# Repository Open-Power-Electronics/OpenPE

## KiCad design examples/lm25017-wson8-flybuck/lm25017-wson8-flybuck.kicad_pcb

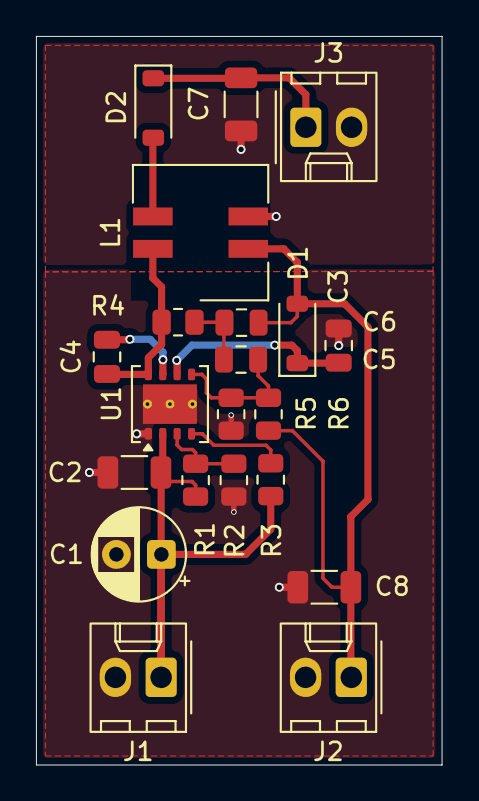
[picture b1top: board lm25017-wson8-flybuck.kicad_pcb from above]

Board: 2 copper layers, 22.5 x 40.5 mm, 21 parts (0 on the bottom side), 13 nets.

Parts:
C1: 2.2uF; CP_Radial_D5.0mm_P2.50mm
C2: 0.47uF; C_1206_3216Metric
C3: 0.1uF; C_0805_2012Metric
C4: 0.01uF; C_0805_2012Metric
C5: 10nF; C_0805_2012Metric
C6: 1nF; C_0805_2012Metric
C7: 2.2uF; C_1206_3216Metric
C8: 4.7uF; C_1206_3216Metric
D1, D2: D; D_SOD-123
J1, J2, J3: Conn_01x02; Molex_KK-254_AE-6410-02A_1x02_P2.54mm_Vertical
L1: 100uH; L_Wurth_WE-DD-7345straight
R1: 127k; R_0805_2012Metric
R2: 11.8k; R_0805_2012Metric
R3: 124k; R_0805_2012Metric
R4: 46.4k; R_0805_2012Metric
R5: 100k; R_0805_2012Metric
R6: 24.9k; R_0805_2012Metric
U1: LM25017; WSON-8-1EP_4x4mm_P0.8mm_EP2.2x3mm_ThermalVias

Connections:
/VIN: C1.1, C2.1, J1.1, R1.2, R3.1, U1.2
/VOUT1: C6.1, C8.1, D1.2, J2.1, L1.2, R5.1
/VOUT2: C7.1, D2.1, J3.1
GND: C1.2, C2.2, C3.2, C8.2, J1.2, J2.2, R2.1, R6.2, U1.1, U1.9
GND2: C7.2, J3.2, L1.3
unnamed: C5.1, C6.2, R4.2
unnamed: C3.1, D1.1, U1.6
unnamed: D2.2, L1.4
unnamed: C4.2, U1.7
unnamed: C5.2, R5.2, R6.1, U1.5
unnamed: R3.2, U1.4
unnamed: C4.1, L1.1, R4.1, U1.8
unnamed: R1.1, R2.2, U1.3

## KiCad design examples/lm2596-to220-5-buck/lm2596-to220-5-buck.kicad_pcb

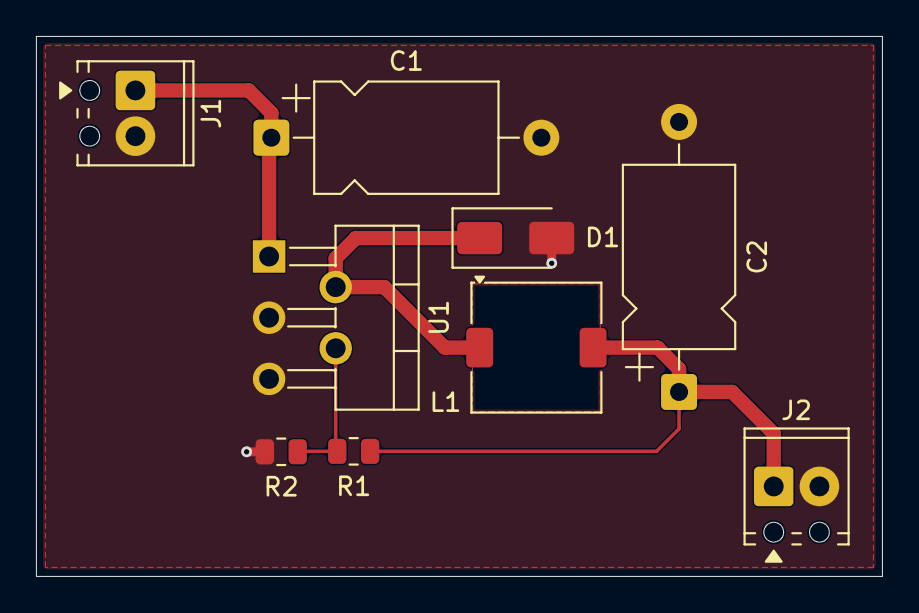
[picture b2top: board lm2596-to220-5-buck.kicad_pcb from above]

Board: 2 copper layers, 47.0 x 30.0 mm, 9 parts (0 on the bottom side), 5 nets.

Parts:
C1: 100uF; CP_Axial_L10.0mm_D6.0mm_P15.00mm_Horizontal
C2: 330uF; CP_Axial_L10.0mm_D6.0mm_P15.00mm_Horizontal
D1: D_Schottky; D_SMA
J1, J2: Conn_01x02; TerminalBlock_Phoenix_MPT-0,5-2-2.54_1x02_P2.54mm_Horizontal
L1: 330uH; L_TDK_SLF7032
R1: 3.09k; R_0805_2012Metric
R2: 1.01k; R_0805_2012Metric
U1: LM2596T-ADJ; TO-220-5_P3.4x3.7mm_StaggerOdd_Lead3.8mm_Vertical

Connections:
/VIN: C1.1, J1.1, U1.1
/VOUT: C2.1, J2.1, L1.2, R1.1
GND: C1.2, C2.2, D1.2, J1.2, J2.2, R2.2, U1.3, U1.5
unnamed: D1.1, L1.1, U1.2
unnamed: R1.2, R2.1, U1.4

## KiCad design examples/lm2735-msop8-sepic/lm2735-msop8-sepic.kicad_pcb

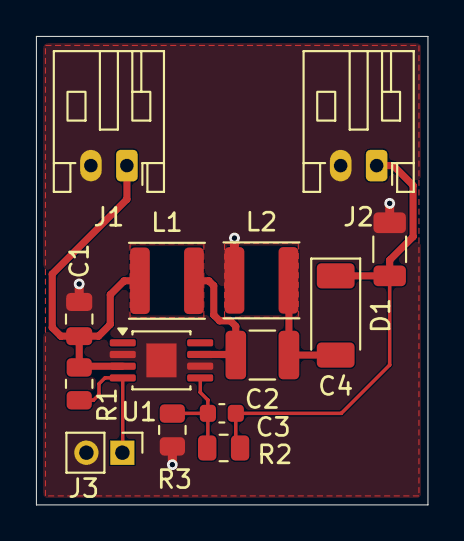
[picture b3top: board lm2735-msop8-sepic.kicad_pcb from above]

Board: 2 copper layers, 21.8 x 26.0 mm, 14 parts (0 on the bottom side), 7 nets.

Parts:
C1: 10uF; C_0805_2012Metric
C2: 10uF; C_1210_3225Metric
C3: 330pF; C_0603_1608Metric
C4: 10uF; C_1206_3216Metric
D1: D_Schottky; D_SOD-128
J1, J2: Conn_01x02; JST_PH_S2B-PH-K_1x02_P2.00mm_Horizontal
J3: Conn_01x02; PinHeader_1x02_P2.00mm_Vertical
L1, L2: 10uH; L_APV_ANR4030
R1: 649k; R_0805_2012Metric
R2: 180k; R_0805_2012Metric
R3: 60.4k; R_0805_2012Metric
U1: LM2735Y; MSOP-8-1EP_3x3mm_P0.65mm_EP1.68x1.88mm

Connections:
/EN: J3.1, R1.2, U1.4
/VIN: C1.1, J1.1, L1.1, R1.1, U1.3
/VOUT: C3.2, C4.1, D1.1, J2.1, R2.1
GND: C1.2, C4.2, J1.2, J2.2, J3.2, L2.1, R3.2, U1.2, U1.6, U1.9
unnamed: C2.1, D1.2, L2.2
unnamed: C3.1, R2.2, R3.1, U1.5
unnamed: C2.2, L1.2, U1.7

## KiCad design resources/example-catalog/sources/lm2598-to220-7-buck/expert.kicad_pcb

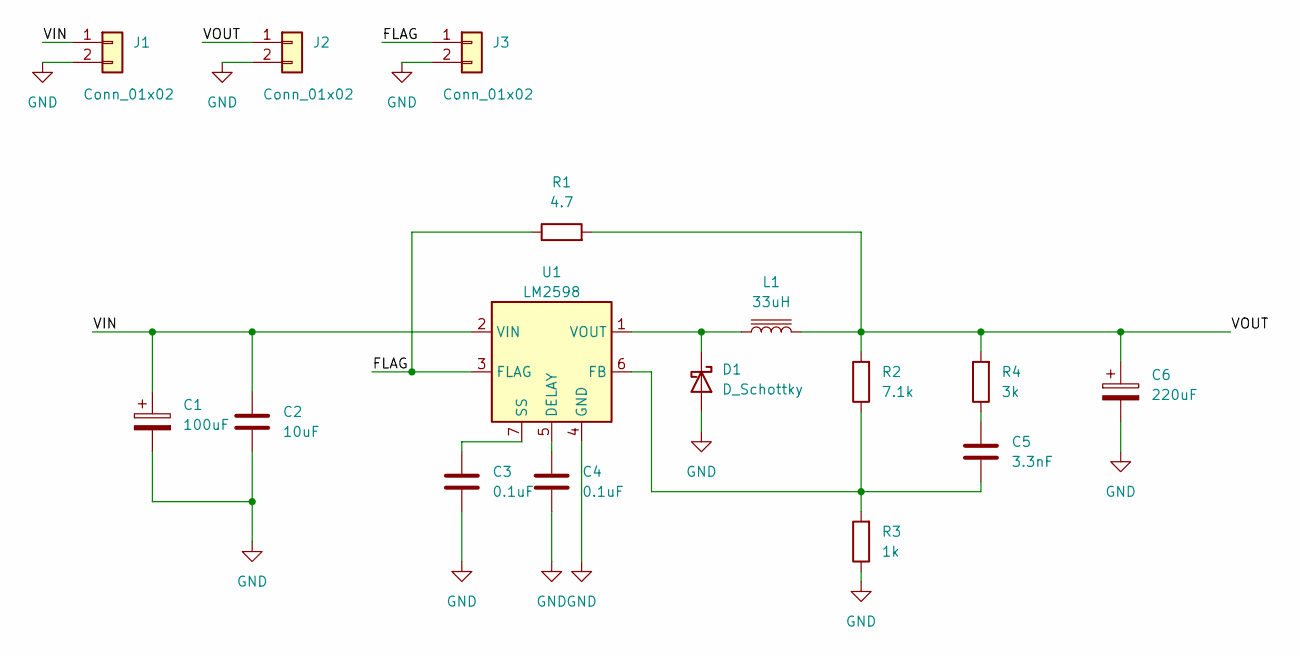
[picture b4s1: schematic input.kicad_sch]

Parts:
C1: 100uF; CP_Elec_6.3x5.2
C2: 10uF; C_1206_3216Metric
C3, C4: 0.1uF; C_0805_2012Metric
C5: 3.3nF; C_0805_2012Metric
C6: 220uF; CP_Elec_6.3x5.2
D1: D_Schottky; D_SMB
J1, J2: Conn_01x02; TerminalBlock_Phoenix_PT-1,5-2-5.0-H_1x02_P5.00mm_Horizontal
J3: Conn_01x02; PinHeader_1x02_P2.00mm_Vertical
L1: 33uH; L_Changjiang_FXL1050
R1: 4.7; R_0805_2012Metric
R2: 7.1k; R_0805_2012Metric
R3: 1k; R_0805_2012Metric
R4: 3k; R_0805_2012Metric
U1: LM2598; TO-220-7_P2.54x5.08mm_StaggerOdd_Lead3.08mm_Vertical

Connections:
/FLAG: J3.1, R1.1, U1.3 (FLAG)
/VIN: C1.1, C2.1, J1.1, U1.2 (VIN)
/VOUT: C6.1, J2.1, L1.2, R1.2, R2.2, R4.2
GND: C1.2, C2.2, C3.2, C4.2, C6.2, D1.2 (A), J1.2, J2.2, J3.2, R3.1, U1.4 (GND)
unnamed: C5.2, R4.1
unnamed: D1.1 (K), L1.1, U1.1 (VOUT)
unnamed: C4.1, U1.5 (DELAY)
unnamed: C5.1, R2.1, R3.2, U1.6 (FB)
unnamed: C3.1, U1.7 (SS)

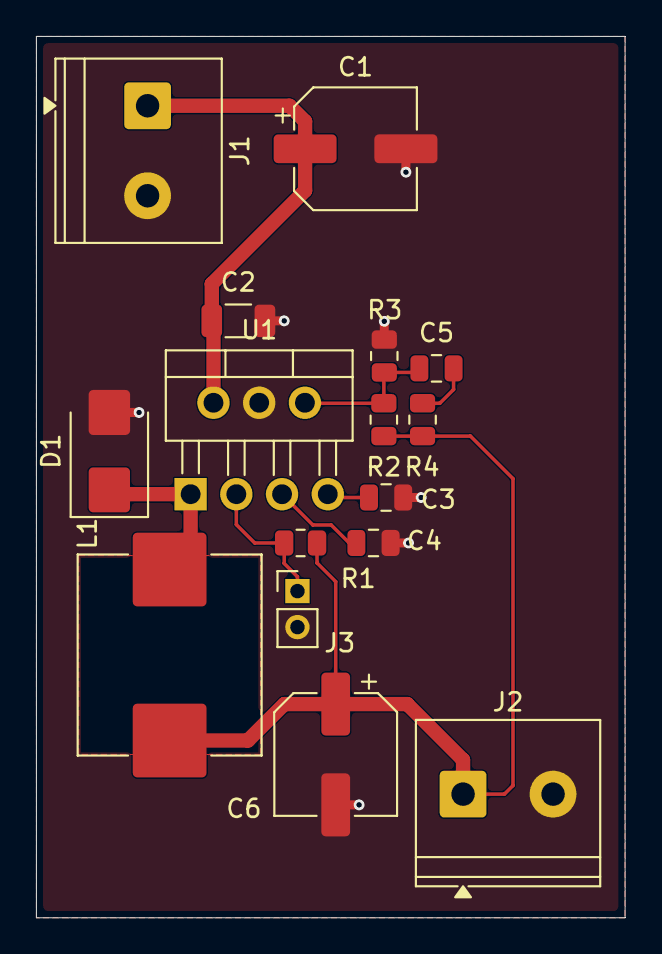
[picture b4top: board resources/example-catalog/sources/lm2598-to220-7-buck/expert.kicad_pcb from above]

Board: 2 copper layers, 32.7 x 49.0 mm, 16 parts (0 on the bottom side), 9 nets.

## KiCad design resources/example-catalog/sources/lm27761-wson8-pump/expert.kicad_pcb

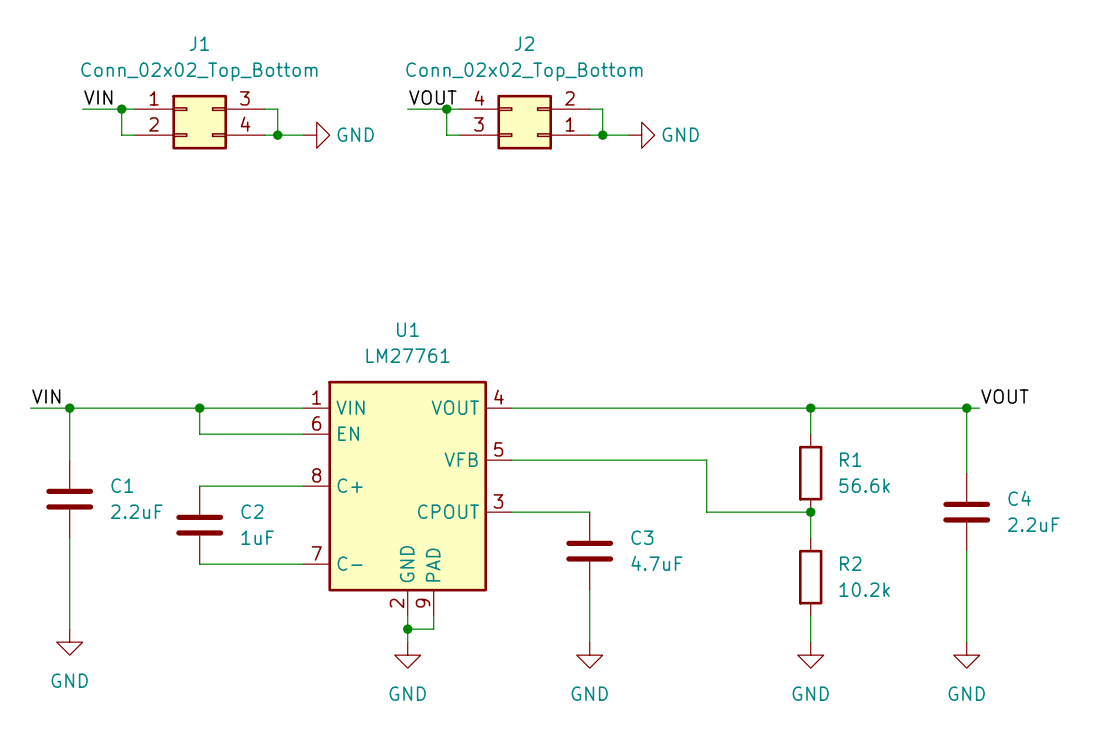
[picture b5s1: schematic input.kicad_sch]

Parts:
C1, C4: 2.2uF; C_1206_3216Metric
C2: 1uF; C_1206_3216Metric
C3: 4.7uF; C_0805_2012Metric
J1, J2: Conn_02x02_Top_Bottom; Wuerth_WR-PHD_613004216921_Large_2x02_P2.54mm_Vertical
R1: 56.6k; R_0805_2012Metric
R2: 10.2k; R_0805_2012Metric
U1: LM27761; WSON-8-1EP_2x2mm_P0.5mm_EP0.9x1.6mm

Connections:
/VIN: C1.1, J1.1, J1.2, U1.1 (VIN), U1.6 (EN)
/VOUT: C4.1, J2.3, J2.4, R1.1, U1.4 (VOUT)
GND: C1.2, C3.2, C4.2, J1.3, J1.4, J2.1, J2.2, R2.2, U1.2 (GND), U1.9 (PAD)
unnamed: C2.1, U1.8 (C+)
unnamed: C2.2, U1.7 (C-)
unnamed: C3.1, U1.3 (CPOUT)
unnamed: R1.2, R2.1, U1.5 (VFB)

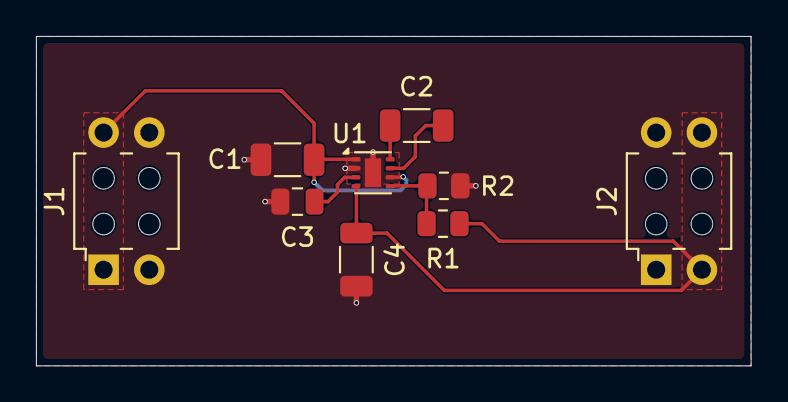
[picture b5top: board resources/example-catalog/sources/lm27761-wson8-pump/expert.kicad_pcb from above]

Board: 2 copper layers, 39.7 x 18.3 mm, 9 parts (0 on the bottom side), 7 nets.
